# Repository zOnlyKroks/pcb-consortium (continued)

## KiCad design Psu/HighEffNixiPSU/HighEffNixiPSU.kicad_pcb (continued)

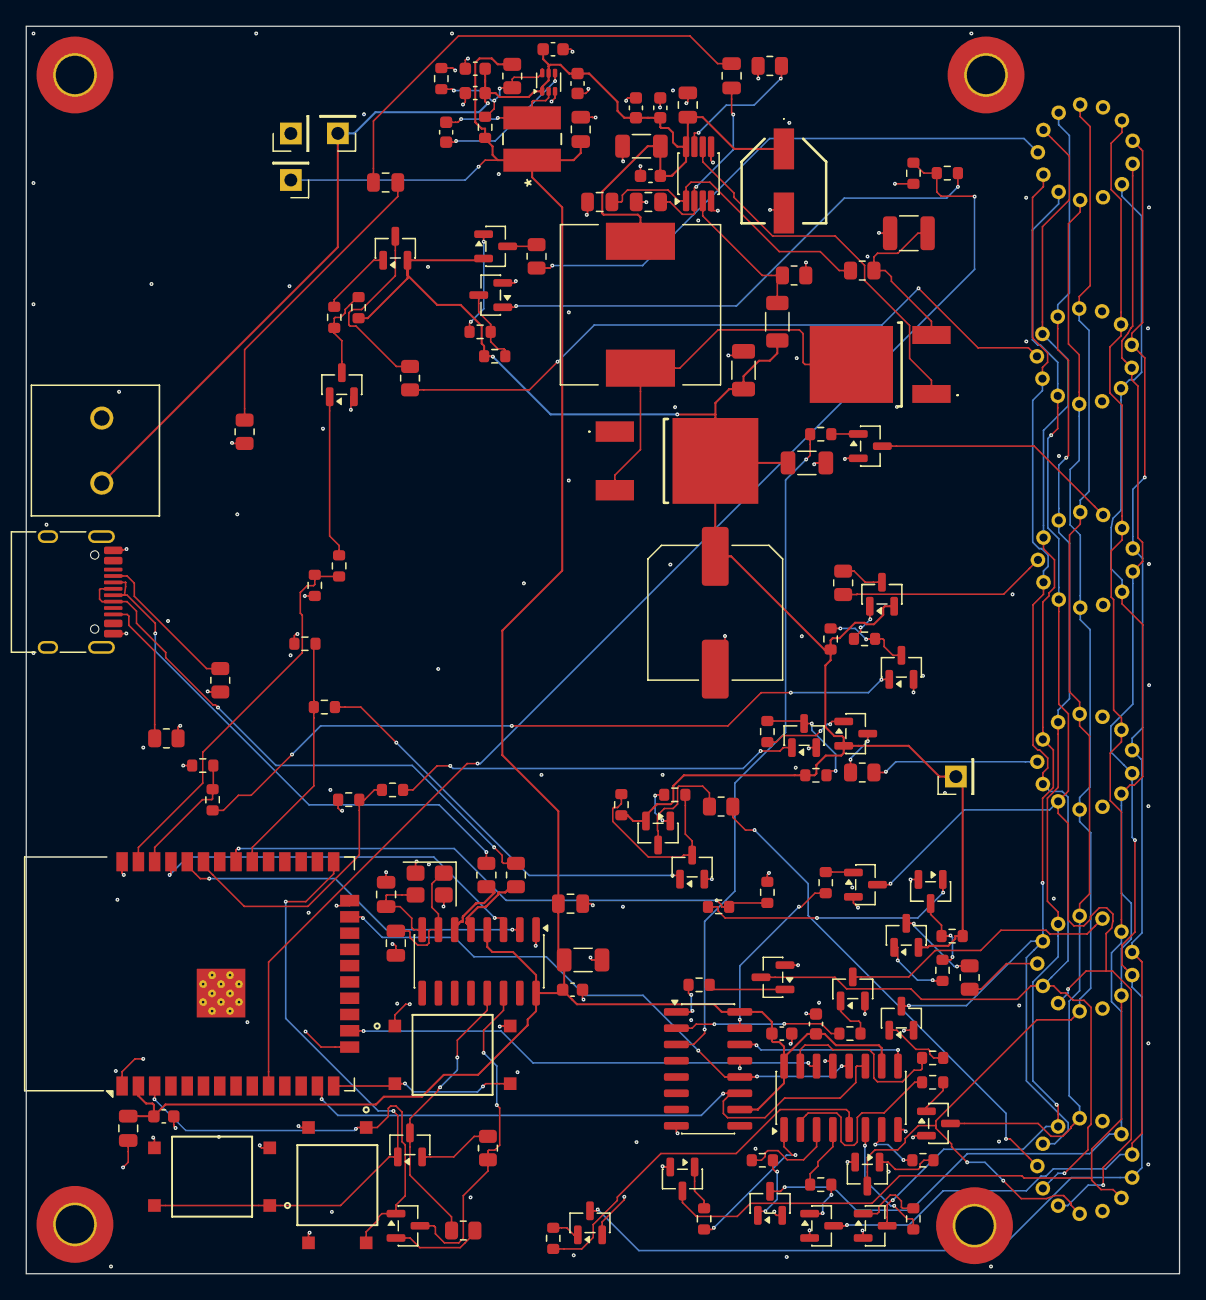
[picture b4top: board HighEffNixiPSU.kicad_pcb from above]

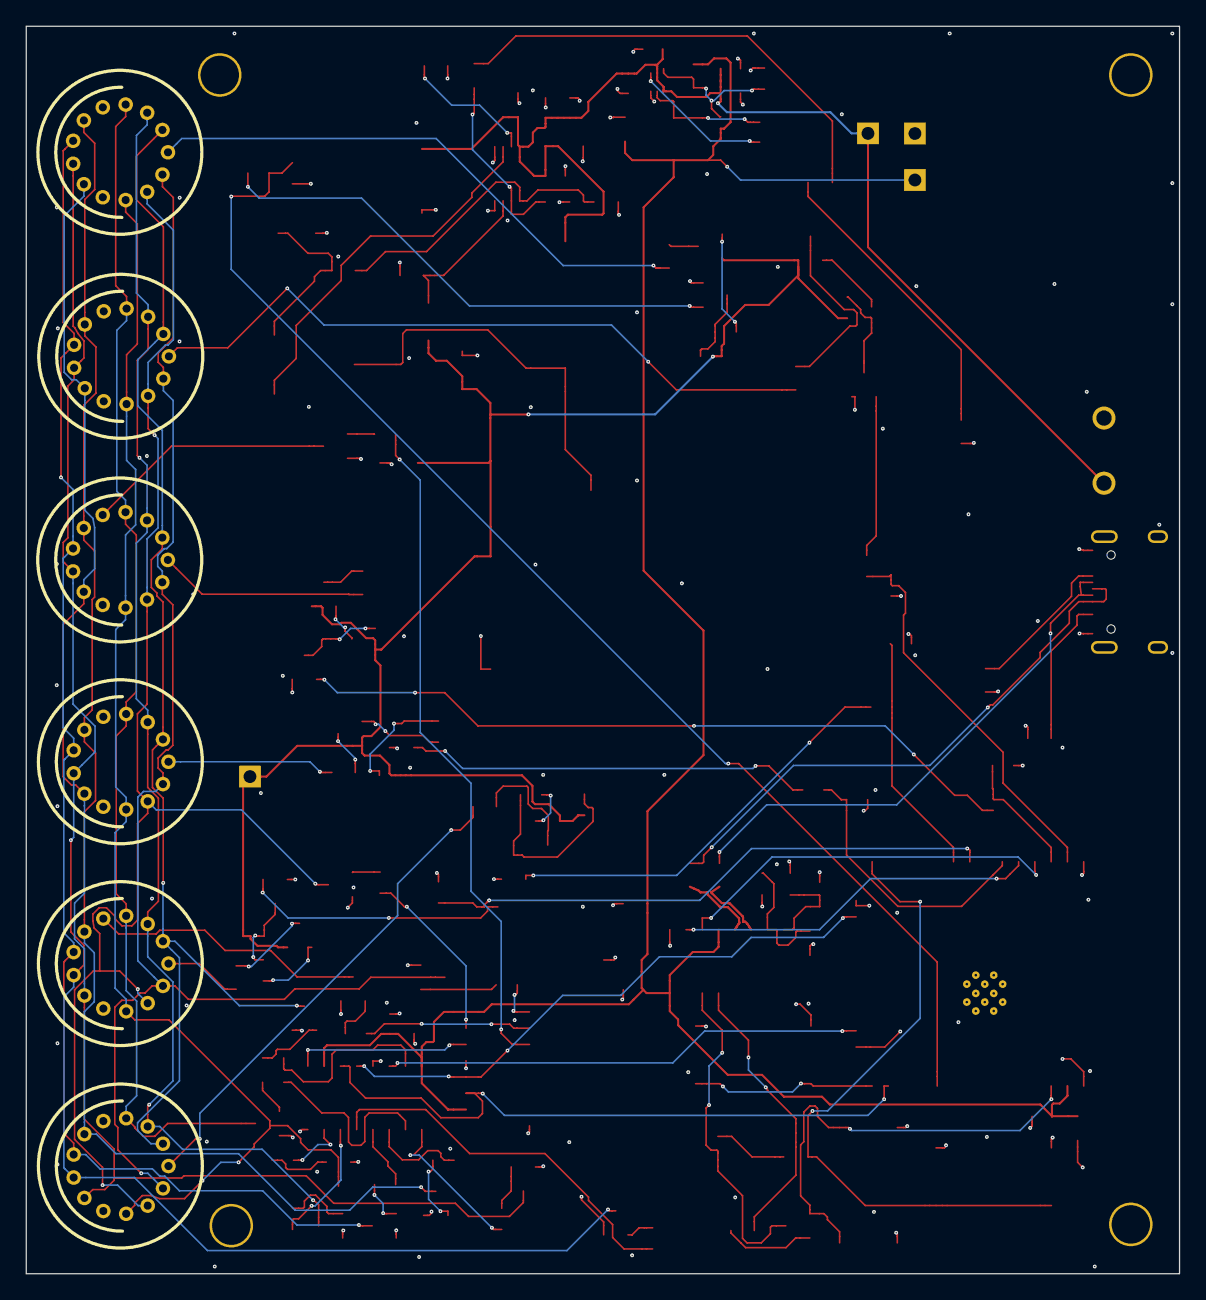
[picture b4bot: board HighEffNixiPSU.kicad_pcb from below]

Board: 4 copper layers, 90.0 x 97.4 mm, 141 parts (6 on the bottom side), 109 nets.

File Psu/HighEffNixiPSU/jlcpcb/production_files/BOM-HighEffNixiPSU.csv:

Comment,Designator,Footprint,LCSC,Quantity
1.2MOhm,Rfb2,R_1206_3216Metric,C36337,1
1.5nF,"Ccomp2,Ccomp3",C_0805_2012Metric,C1717,2
10 pF,Cfilt1,C_0805_2012Metric,C107107,1
10 uF,C6,C_Elec_10x10.2,C48970948,1
100 Ohm,RFilt1,R_0805_2012Metric,C17408,1
100 nF,"C79,C80",C_0805_2012Metric,C49678,2
100k,"R50,R53,R57,R61,R65,R69",R_0603_1608Metric,C25804,6
100nF,"C10,C13,C14,C15,C16,C5,C7,C8",C_0603_1608Metric,C14663,8
100nF,Cbyp1,C_0805_2012Metric,C28233,1
100nF,"C2,C4",C_1206_3216Metric,C365814,2
10k Ohm,"R43,R44",R_0805_2012Metric,C17414,2
10k Ohm,"R27,R28,R29,R30,R31,R32,R33,R34,R35,R36,R37,R38,R47,R48,R51,R52,R55,R56,R59,R60,R63,R64,R67,R68,Rffb1",R_0603_1608Metric,C25804,25
10uF,"C11,C12,C3,C9",C_0603_1608Metric,C19702,4
12 MHz,Y3,Crystal_SMD_3225-4Pin_3.2x2.5mm,C9002,1
12 pF,"C17,C59",C_0805_2012Metric,C1792,2
147 kOhm,Rfadj1,R_0805_2012Metric,C17462,1
15 pF,C19,R_0805_2012Metric,C107110,1
150pF,Ccomp1,C_0805_2012Metric,C1716,1
162 kOhm,Rcomp1,R_0805_2012Metric,C47115899,1
22,"R41,R42",R_0805_2012Metric,C17561,2
22uF,C23,C_0805_2012Metric,C45783,1
30.9 kOhm,Rfbt1,R_0603_1608Metric,C2930090,1
33 mOhm,RSense1,R_1210_3225Metric,C723419,1
33k Ohm,"Br10,Br11,Br12,Br7,Br8,Br9",R_0805_2012Metric,C17633,6
47k Ohm,"R49,R54,R58,R62,R66,R70",R_0603_1608Metric,C25804,6
47uF,"C24,C26",C_1206_3216Metric,C96123,2
5.1k,"R39,R40",R_0805_2012Metric,C27834,2
74HC595,"U2,U5",SOIC-16_3.9x9.9mm_P1.27mm,C10092,2
8.06 kOhm,Rfb1,R_0805_2012Metric,C19006,1
BOOT0,SW5,KH-6X6X5H-STM_SKE,C2837531,1
CAL,SW4,KH-6X6X5H-STM_SKE,C2837531,1
CH340G,U6,SOIC-16_3.9x9.9mm_P1.27mm,C14267,1
CYH127-330UH,L1,CYH127-330UH,C2929508,1
Conn_01x01,"GND1,VIN1,VIN2,VIN3",PinHeader_1x01_P2.54mm_Vertical,C492400,4
EEE-FT1V680AP,C1,EEE1AA101SP,C413520,1
EN,SW3,KH-6X6X5H-STM_SKE,C2837531,1
ESP32-WROOM-32E-R2,U7,ESP32-WROOM-32D,C701343,1
FQD16N25CTM,Q1,FQD16N25CTM,C415866,1
LM3478MM,U1,VSSOP-8_3x3mm_P0.65mm,C9404,1
MMBTA42,"Q10,Q12,Q14,Q16,Q18,Q26,Q27,Q28,Q29,Q30,Q31,Q32,Q33,Q34,Q35,Q36,Q37,Q9",SOT-23,C20069138,18
MMBTA92,"Q11,Q13,Q15,Q17,Q19,Q7",SOT-23,C20069146,6
NPN,SS8050,SOT-23,C431710,1
SDR0403-3R3ML,L2,IND_BOURNS_SDR0403,C139481,1
SS8050,Q8,SOT-23,C2150,1
STTH506B,D1,STTH506BTR,C283501,1
Screw_Terminal_01x02,J1,WJ500V-5.08-2P,C8465,1
TPS562202,U4,SOT-563,C2877547,1
USB_C_Receptacle_USB2.0,J6,USB_C_Receptacle_HRO_TYPE-C-31-M-12,C165948,1
IN-16,N5,nixies-us-IN-16,,1
IN-16,N4,nixies-us-IN-16,,1
IN-16,N6,nixies-us-IN-16,,1
IN-16,N1,nixies-us-IN-16,,1
IN-16,N3,nixies-us-IN-16,,1
IN-16,N2,nixies-us-IN-16,,1

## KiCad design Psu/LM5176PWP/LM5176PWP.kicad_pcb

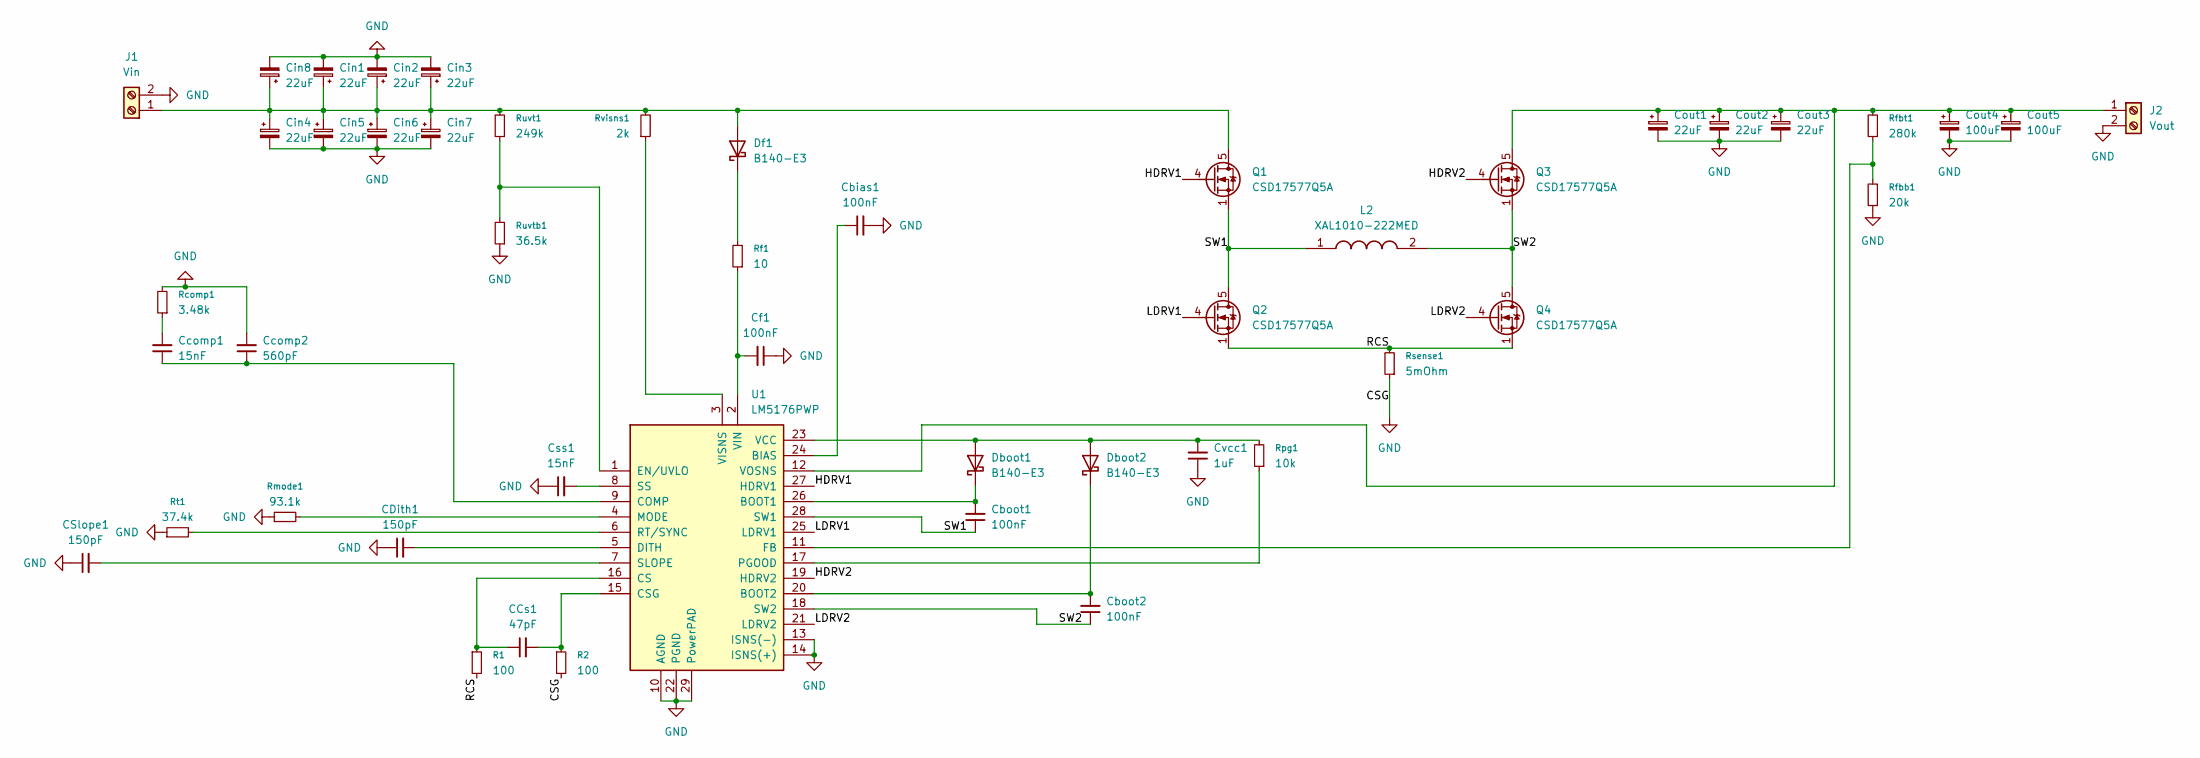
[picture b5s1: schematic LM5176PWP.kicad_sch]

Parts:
CCs1: 47pF; C_0805_2012Metric
CDith1: 150pF; C_0805_2012Metric
CSlope1: 150pF; C_0805_2012Metric
Cbias1: 100nF; C_0805_2012Metric
Cboot1, Cboot2: 100nF; C_0805_2012Metric
Ccomp1: 15nF; C_0805_2012Metric
Ccomp2: 560pF; C_0805_2012Metric
Cf1: 100nF; C_0805_2012Metric
Cin1, Cin2, Cin3, Cin4, Cin5, Cin6, Cin7, Cin8: 22uF; CP_Elec_5x5.4
Cout1, Cout2, Cout3: 22uF; CP_Elec_5x5.4
Cout4, Cout5: 100uF; CP_Elec_6.3x7.7
Css1: 15nF; C_0805_2012Metric
Cvcc1: 1uF; C_0805_2012Metric
Dboot1, Dboot2: B140-E3; D_SMA
Df1: B140-E3; D_SMA
J1: Vin; WJ500V-5.08-2P
J2: Vout; WJ500V-5.08-2P
L2: XAL1010-222MED; XAL1010222MED; Mouser Part Number 994-XAL1010-222MED
Q1, Q2, Q3, Q4: CSD17577Q5A; TDSON-8-1
R1, R2: 100; R_0805_2012Metric
Rcomp1: 3.48k; R_0805_2012Metric
Rf1: 10; R_0805_2012Metric
Rfbb1: 20k; R_0805_2012Metric
Rfbt1: 280k; R_0805_2012Metric
Rmode1: 93.1k; R_0805_2012Metric
Rpg1: 10k; R_0805_2012Metric
Rsense1: 5mOhm; R_0805_2012Metric
Rt1: 37.4k; R_0805_2012Metric
Ruvt1: 249k; R_0805_2012Metric
Ruvtb1: 36.5k; R_0805_2012Metric
Rvisns1: 2k; R_0805_2012Metric
U1: LM5176PWP; HTSSOP-28-1EP_4.4x9.7mm_P0.65mm_EP3.4x9.5mm_ThermalVias

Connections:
/HDRV1: Q1.4 (G), U1.27 (HDRV1)
/HDRV2: Q3.4 (G), U1.19 (HDRV2)
/LDRV1: Q2.4 (G), U1.25 (LDRV1)
/LDRV2: Q4.4 (G), U1.21 (LDRV2)
/RCS: Q2.1 (S), Q2.2 (S), Q2.3 (S), Q4.1 (S), Q4.2 (S), Q4.3 (S), R1.2, Rsense1.2
/SW1: Cboot1.1, L2.1, Q1.1 (S), Q1.2 (S), Q1.3 (S), Q2.5 (D), U1.28 (SW1)
/SW2: Cboot2.1, L2.2, Q3.1 (S), Q3.2 (S), Q3.3 (S), Q4.5 (D), U1.18 (SW2)
GND: CDith1.1, CSlope1.1, Cbias1.2, Ccomp2.2, Cf1.1, Cin1.2, Cin2.2, Cin3.2, Cin4.2, Cin5.2, Cin6.2, Cin7.2, Cin8.2, Cout1.2, Cout2.2, Cout3.2, Cout4.2, Cout5.2, Css1.1, Cvcc1.1, J1.2, J2.2, R2.2, Rcomp1.2, Rfbb1.1, Rmode1.1, Rsense1.1, Rt1.1, Ruvtb1.1, U1.10 (AGND), U1.13 (ISNS(-)), U1.14 (ISNS(+)), U1.22 (PGND), U1.29 (PowerPAD)
unnamed: Ccomp1.2, Rcomp1.1
unnamed: Cvcc1.2, Dboot1.2 (A), Dboot2.2 (A), Rpg1.2, U1.23 (VCC)
unnamed: Cboot1.2, Dboot1.1 (K), U1.26 (BOOT1)
unnamed: Cboot2.2, Dboot2.1 (K), U1.20 (BOOT2)
unnamed: Cin1.1, Cin2.1, Cin3.1, Cin4.1, Cin5.1, Cin6.1, Cin7.1, Cin8.1, Df1.2 (A), J1.1, Q1.5 (D), Ruvt1.2, Rvisns1.2
unnamed: Df1.1 (K), Rf1.2
unnamed: Cout1.1, Cout2.1, Cout3.1, Cout4.1, Cout5.1, J2.1, Q3.5 (D), Rfbt1.2, U1.12 (VOSNS)
unnamed: Cbias1.1, U1.24 (BIAS)
unnamed: Ccomp1.1, Ccomp2.1, U1.9 (COMP)
unnamed: CCs1.1, R1.1, U1.16 (CS)
unnamed: CCs1.2, R2.1, U1.15 (CSG)
unnamed: CDith1.2, U1.5 (DITH)
unnamed: Ruvt1.1, Ruvtb1.2, U1.1 (EN/UVLO)
unnamed: Rfbb1.2, Rfbt1.1, U1.11 (FB)
unnamed: Rmode1.2, U1.4 (MODE)
unnamed: Rpg1.1, U1.17 (PGOOD)
unnamed: Rt1.2, U1.6 (RT/SYNC)
unnamed: CSlope1.2, U1.7 (SLOPE)
unnamed: Css1.2, U1.8 (SS)
unnamed: Cf1.2, Rf1.1, U1.2 (VIN)
unnamed: Rvisns1.1, U1.3 (VISNS)

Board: 4 copper layers, 48 parts (0 on the bottom side), 29 nets, no tracks yet.

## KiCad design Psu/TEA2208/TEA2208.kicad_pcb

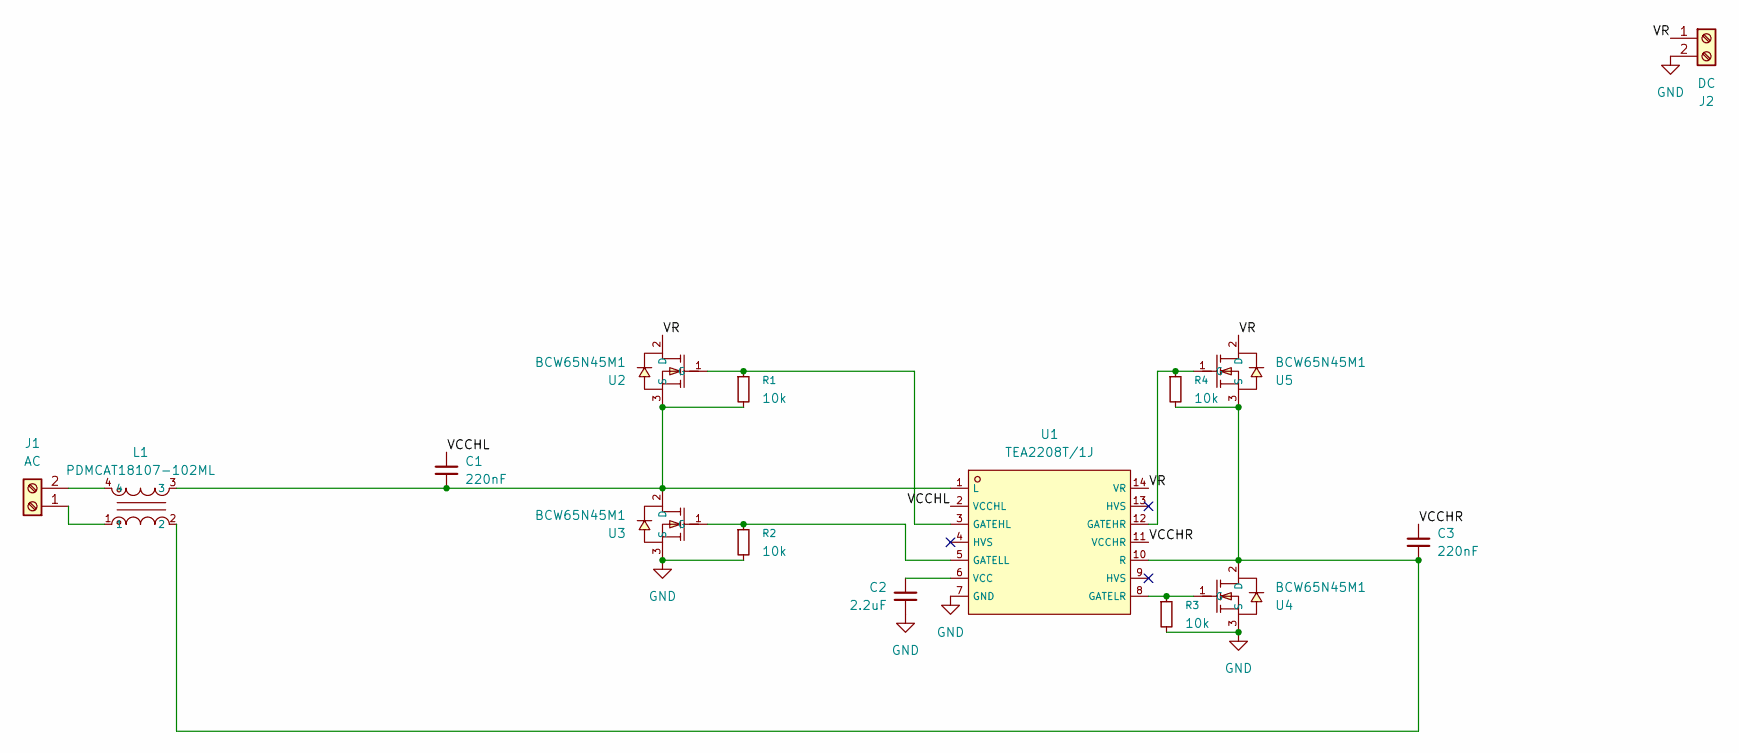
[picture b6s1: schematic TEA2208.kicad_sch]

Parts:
C1, C3: 220nF; C_0603_1608Metric
C2: 2.2uF; C_0603_1608Metric
J1: AC; WJ500V-5.08-2P
J2: DC; WJ500V-5.08-2P
L1: PDMCAT18107-102ML; C2831472_IND-SMD_4P-L22_0-W12_0-P8_00-S9_00; LCSC C2831472
R1, R2, R3, R4: 10k; R_0603_1608Metric
U1: TEA2208T/1J; C1513000_SO-14_L8_7-W3_9-P1_27-LS6_0-BL; LCSC C1513000
U2, U3, U4, U5: BCW65N45M1; C47715867_TO-247-3_L15_8-W5_0-P5_44-L_IXFH16N80P; LCSC C47715867

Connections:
/VCCHL: C1.1, U1.2 (VCCHL)
/VCCHR: C3.1, U1.11 (VCCHR)
/VR: J2.1, U1.14 (VR), U2.2 (D), U5.2 (D)
GND: C2.2, J2.2, R2.2, R3.2, U1.7 (GND), U3.3 (S), U4.3 (S)
unnamed: J1.1, L1.1
unnamed: J1.2, L1.4
unnamed: R1.1, U1.3 (GATEHL), U2.1 (G)
unnamed: R4.1, U1.12 (GATEHR), U5.1 (G)
unnamed: R2.1, U1.5 (GATELL), U3.1 (G)
unnamed: R3.1, U1.8 (GATELR), U4.1 (G)
unnamed: C1.2, L1.3, R1.2, U1.1 (L), U2.3 (S), U3.2 (D)
unnamed: C3.2, L1.2, R4.2, U1.10 (R), U4.2 (D), U5.3 (S)
unnamed: C2.1, U1.6 (VCC)

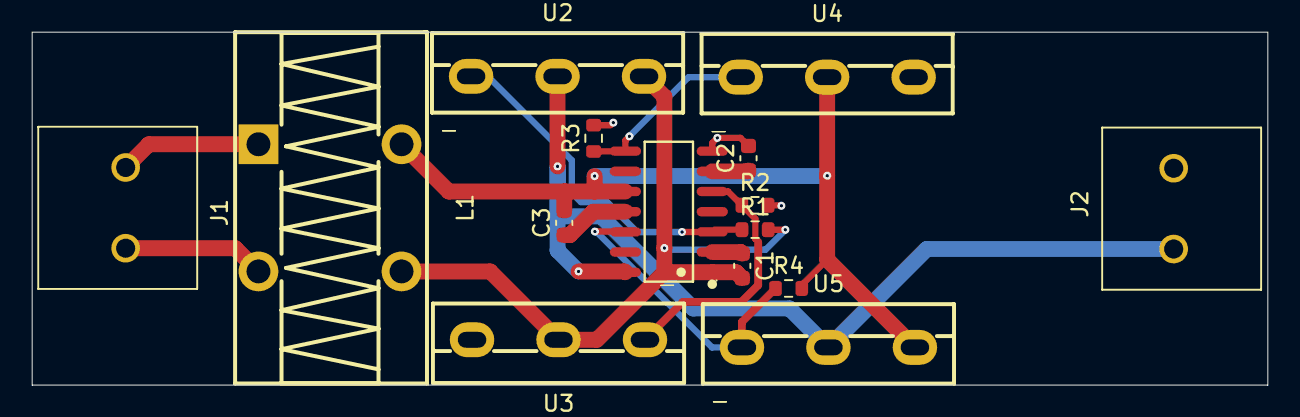
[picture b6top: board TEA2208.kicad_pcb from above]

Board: 4 copper layers, 77.7 x 22.2 mm, 15 parts (0 on the bottom side), 13 nets.

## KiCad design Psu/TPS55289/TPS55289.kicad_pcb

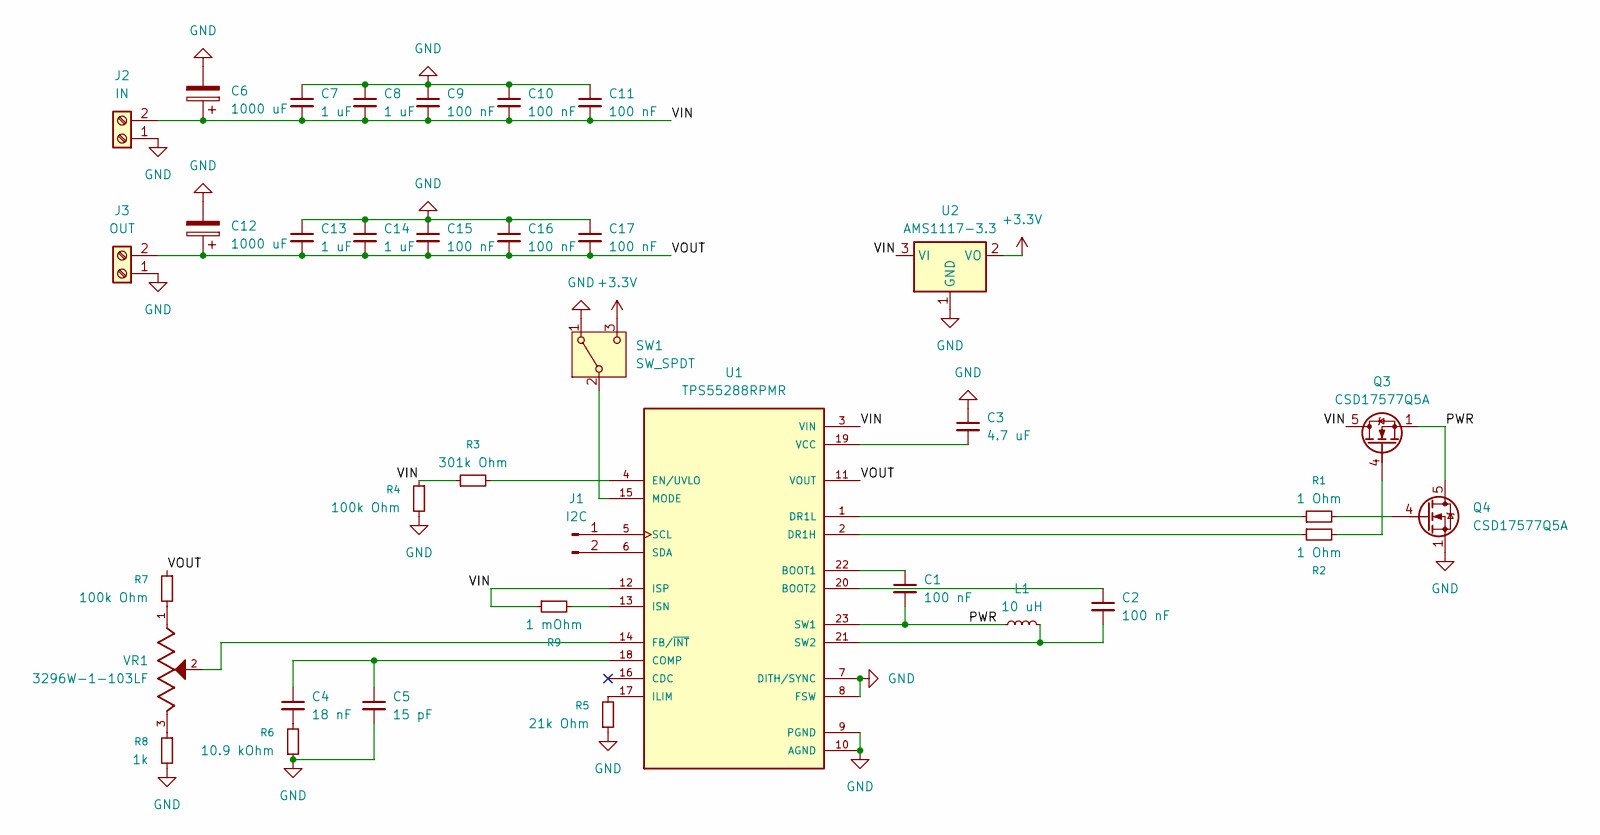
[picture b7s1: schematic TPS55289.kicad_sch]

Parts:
C1, C2, C9, C10, C11, C15, C16, C17: 100 nF; C_0603_1608Metric
C3: 4.7 uF; C_0603_1608Metric
C4: 18 nF; C_0603_1608Metric
C5: 15 pF; C_0603_1608Metric
C6, C12: 1000 uF; CP_Radial_D12.5mm_P5.00mm
C7, C8, C13, C14: 1 uF; C_0805_2012Metric
J1: I2C; PinHeader_1x02_P2.54mm_Vertical
J2: IN; WJ500V-5.08-2P
J3: OUT; WJ500V-5.08-2P
L1: 10 uH; L_6.3x6.3_H3
Q3, Q4: CSD17577Q5A; TDSON-8-1
R1, R2: 1 Ohm; R_0603_1608Metric
R3: 301k Ohm; R_0603_1608Metric
R4, R7: 100k Ohm; R_0603_1608Metric
R5: 21k Ohm; R_0603_1608Metric
R6: 10.9 kOhm; R_0603_1608Metric
R8: 1k; R_0603_1608Metric
R9: 1 mOhm; R_0603_1608Metric
SW1: SW_SPDT
U1: TPS55288RPMR; IC_TPS55288RPMR; PARTREV B
U2: AMS1117-3.3; SOT-223-3_TabPin2
VR1: 3296W-1-103LF; TRIM_3296W-1-103LF; PARTREV 05/16; LCSC Part # C49190453

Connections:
+3.3V: SW1.3 (C), U2.2 (VO); also elsewhere on the board
/PWR: C1.2, L1.1, Q3.1 (S), Q3.2 (S), Q3.3 (S), Q4.5 (D), U1.23 (SW1)
/VIN: C6.1, C7.2, C8.2, C9.2, C10.2, C11.2, J2.2, Q3.5 (D), R3.1, R4.1, R9.1, U1.3 (VIN), U1.12 (ISP), U2.3 (VI)
/VOUT: C12.1, C13.2, C14.2, C15.2, C16.2, C17.2, J3.2, R7.1, U1.11 (VOUT), U1.26 (VOUT)
GND: C3.1, C5.2, C6.2, C7.1, C8.1, C9.1, C10.1, C11.1, C12.2, C13.1, C14.1, C15.1, C16.1, C17.1, J2.1, J3.1, Q4.1 (S), Q4.2 (S), Q4.3 (S), R4.2, R5.1, R6.1, R8.2, SW1.1 (A), U1.7 (DITH/SYNC), U1.8 (FSW), U1.9 (PGND), U1.10 (AGND), U1.24 (PGND), U2.1 (GND); also elsewhere on the board
unnamed: C2.2, L1.2, U1.21 (SW2), U1.25 (SW2)
unnamed: C4.2, R6.2
unnamed: J1.1, U1.5 (SCL)
unnamed: J1.2, U1.6 (SDA)
unnamed: Q3.4 (G), R2.2
unnamed: Q4.4 (G), R1.2
unnamed: R7.2, VR1.1
unnamed: R8.1, VR1.3
unnamed: C1.1, U1.22 (BOOT1)
unnamed: C2.1, U1.20 (BOOT2)
unnamed: C4.1, C5.1, U1.18 (COMP)
unnamed: R2.1, U1.2 (DR1H)
unnamed: R1.1, U1.1 (DR1L)
unnamed: R3.2, U1.4 (EN/UVLO)
unnamed: U1.14 (FB/~INT), VR1.2
unnamed: R5.2, U1.17 (ILIM)
unnamed: R9.2, U1.13 (ISN)
unnamed 22: SW1.2 (B), U1.15 (MODE); also elsewhere on the board
unnamed: C3.2, U1.19 (VCC)

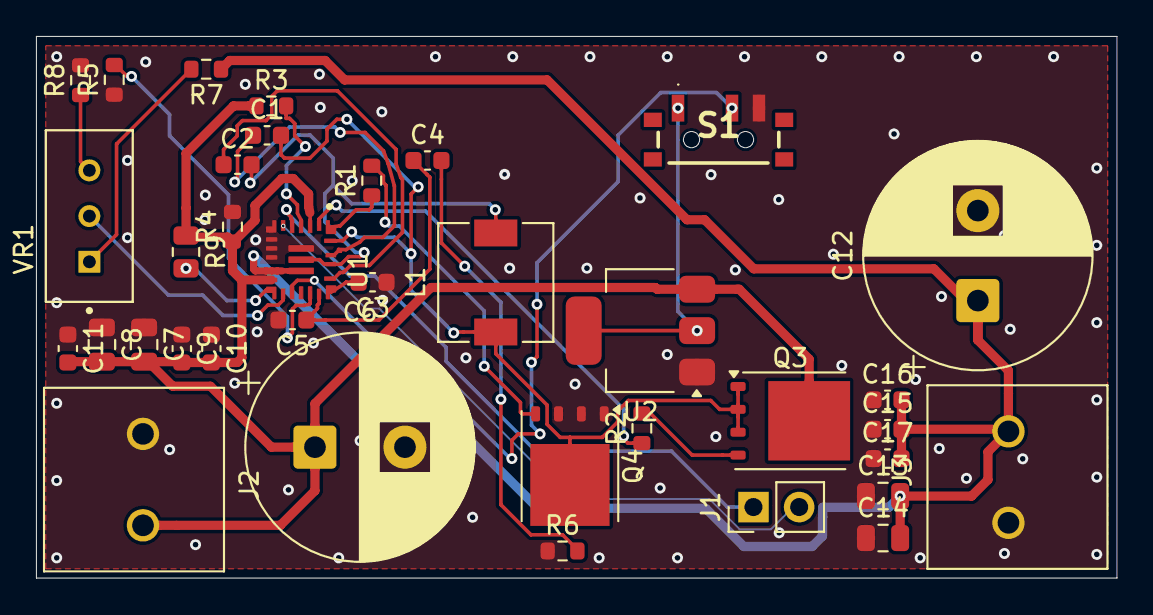
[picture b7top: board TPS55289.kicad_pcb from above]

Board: 2 copper layers, 60.0 x 30.1 mm, 36 parts (0 on the bottom side), 24 nets.

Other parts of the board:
S1: SSSS811101

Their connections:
+3.3V: S1.1; also elsewhere on the board
GND: S1.3; also elsewhere on the board
unnamed 22: S1.2; also elsewhere on the board

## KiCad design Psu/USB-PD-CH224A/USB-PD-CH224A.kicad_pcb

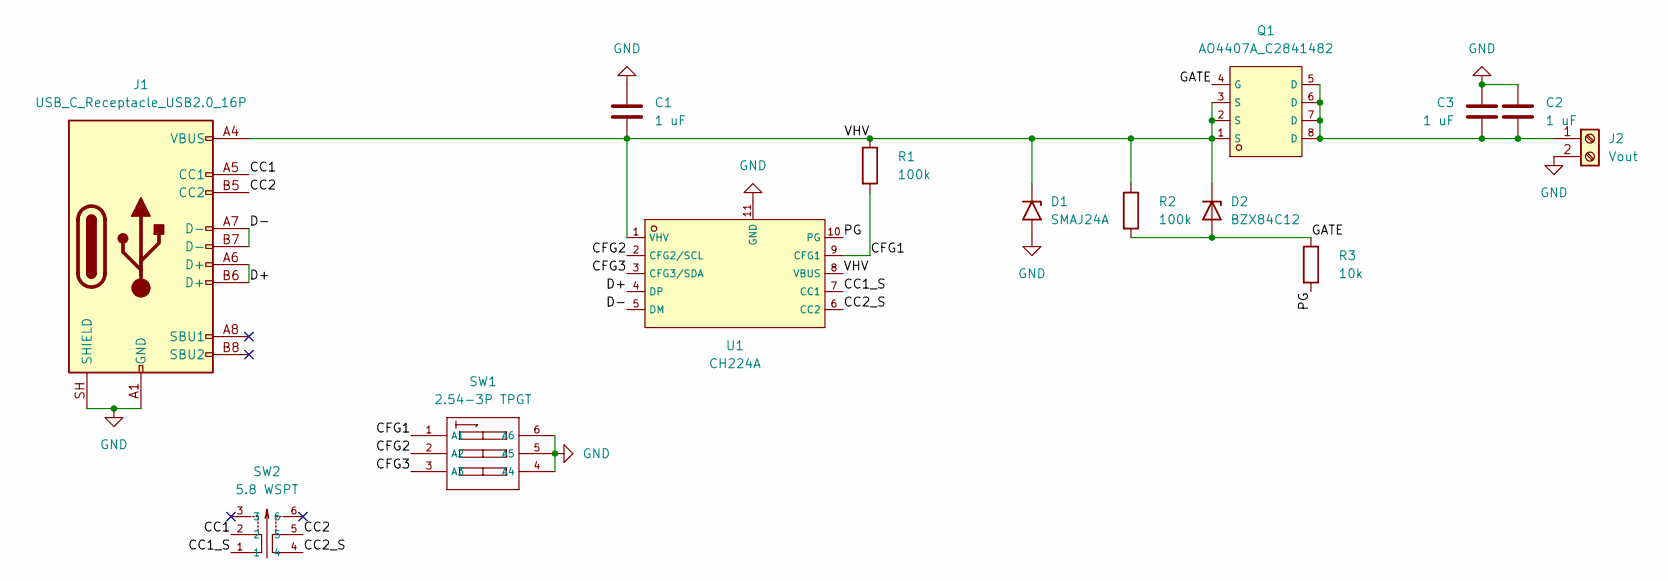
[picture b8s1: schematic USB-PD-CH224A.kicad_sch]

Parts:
C1, C2, C3: 1 uF; C_0805_2012Metric
D1: SMAJ24A; D_SMA
D2: BZX84C12; SOT-23
J1: USB_C_Receptacle_USB2.0_16P; USB_C_Receptacle_HRO_TYPE-C-31-M-12
J2: Vout; WJ500V-5.08-2P
Q1: AO4407A_C2841482; C2841482_SOP-8_L5_0-W4_0-P1_27-LS6_0-BL; LCSC C2841482
R1, R2: 100k; R_0805_2012Metric
R3: 10k; R_0805_2012Metric
SW1: 2.54-3P TPGT; C7421520_SW-SMD_6P-L7_6-W6_0-P2_54-LS9_3-BL; LCSC C7421520
SW2: 5.8 WSPT; C5379898_SW-TH_6P-L5_8-W5_8-P2_00-LS4_5-TL_K8-5851E-L1; LCSC C5379898
U1: CH224A; C42459160_ESSOP-10_L4_9-W3_9-P1_0-LS6_0-TL-EP; LCSC C42459160

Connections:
/CC1: J1.A5 (CC1), SW2.2
/CC1_S: SW2.1, U1.7 (CC1)
/CC2: J1.B5 (CC2), SW2.5
/CC2_S: SW2.4, U1.6 (CC2)
/CFG1: R1.2, SW1.1 (A1), U1.9 (CFG1)
/CFG2: SW1.2 (A2), U1.2 (CFG2/SCL)
/CFG3: SW1.3 (A3), U1.3 (CFG3/SDA)
/D+: J1.A6 (D+), J1.B6 (D+), U1.4 (DP)
/D-: J1.A7 (D-), J1.B7 (D-), U1.5 (DM)
/GATE: D2.1 (A), Q1.4 (G), R2.2, R3.1
/PG: R3.2, U1.10 (PG)
/VHV: C1.2, D1.1 (A1), D2.3 (K), J1.A4 (VBUS), J1.A9 (VBUS), J1.B4 (VBUS), J1.B9 (VBUS), Q1.1 (S), Q1.2 (S), Q1.3 (S), R1.1, R2.1, U1.1 (VHV), U1.8 (VBUS)
GND: C1.1, C2.1, C3.1, D1.2 (A2), J1.A1 (GND), J1.A12 (GND), J1.B1 (GND), J1.B12 (GND), J1.SH (SHIELD), J2.2, SW1.4 (A4), SW1.5 (A5), SW1.6 (A6), U1.11 (GND)
unnamed: C2.2, C3.2, J2.1, Q1.5 (D), Q1.6 (D), Q1.7 (D), Q1.8 (D)

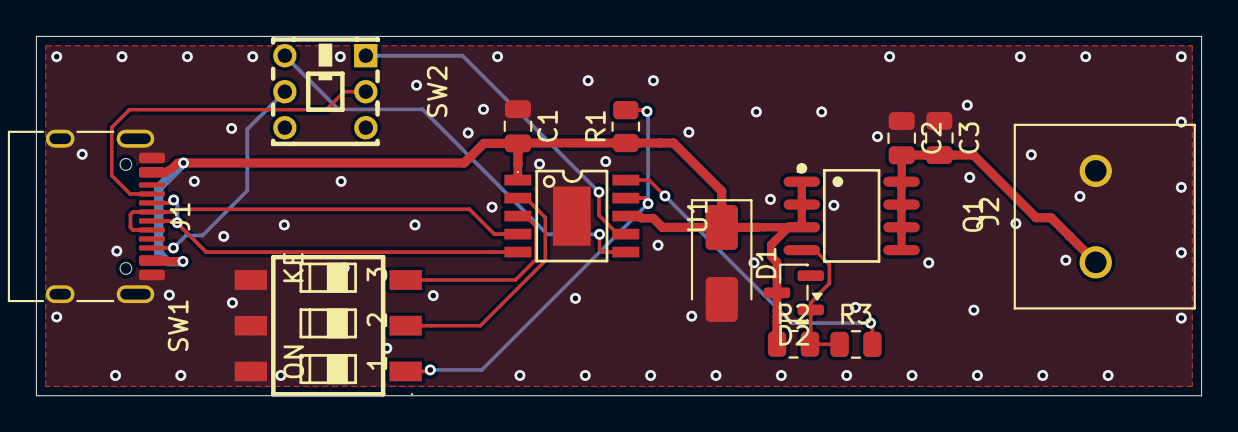
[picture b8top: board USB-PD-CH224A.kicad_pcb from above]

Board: 2 copper layers, 64.7 x 20.0 mm, 14 parts (0 on the bottom side), 14 nets.
